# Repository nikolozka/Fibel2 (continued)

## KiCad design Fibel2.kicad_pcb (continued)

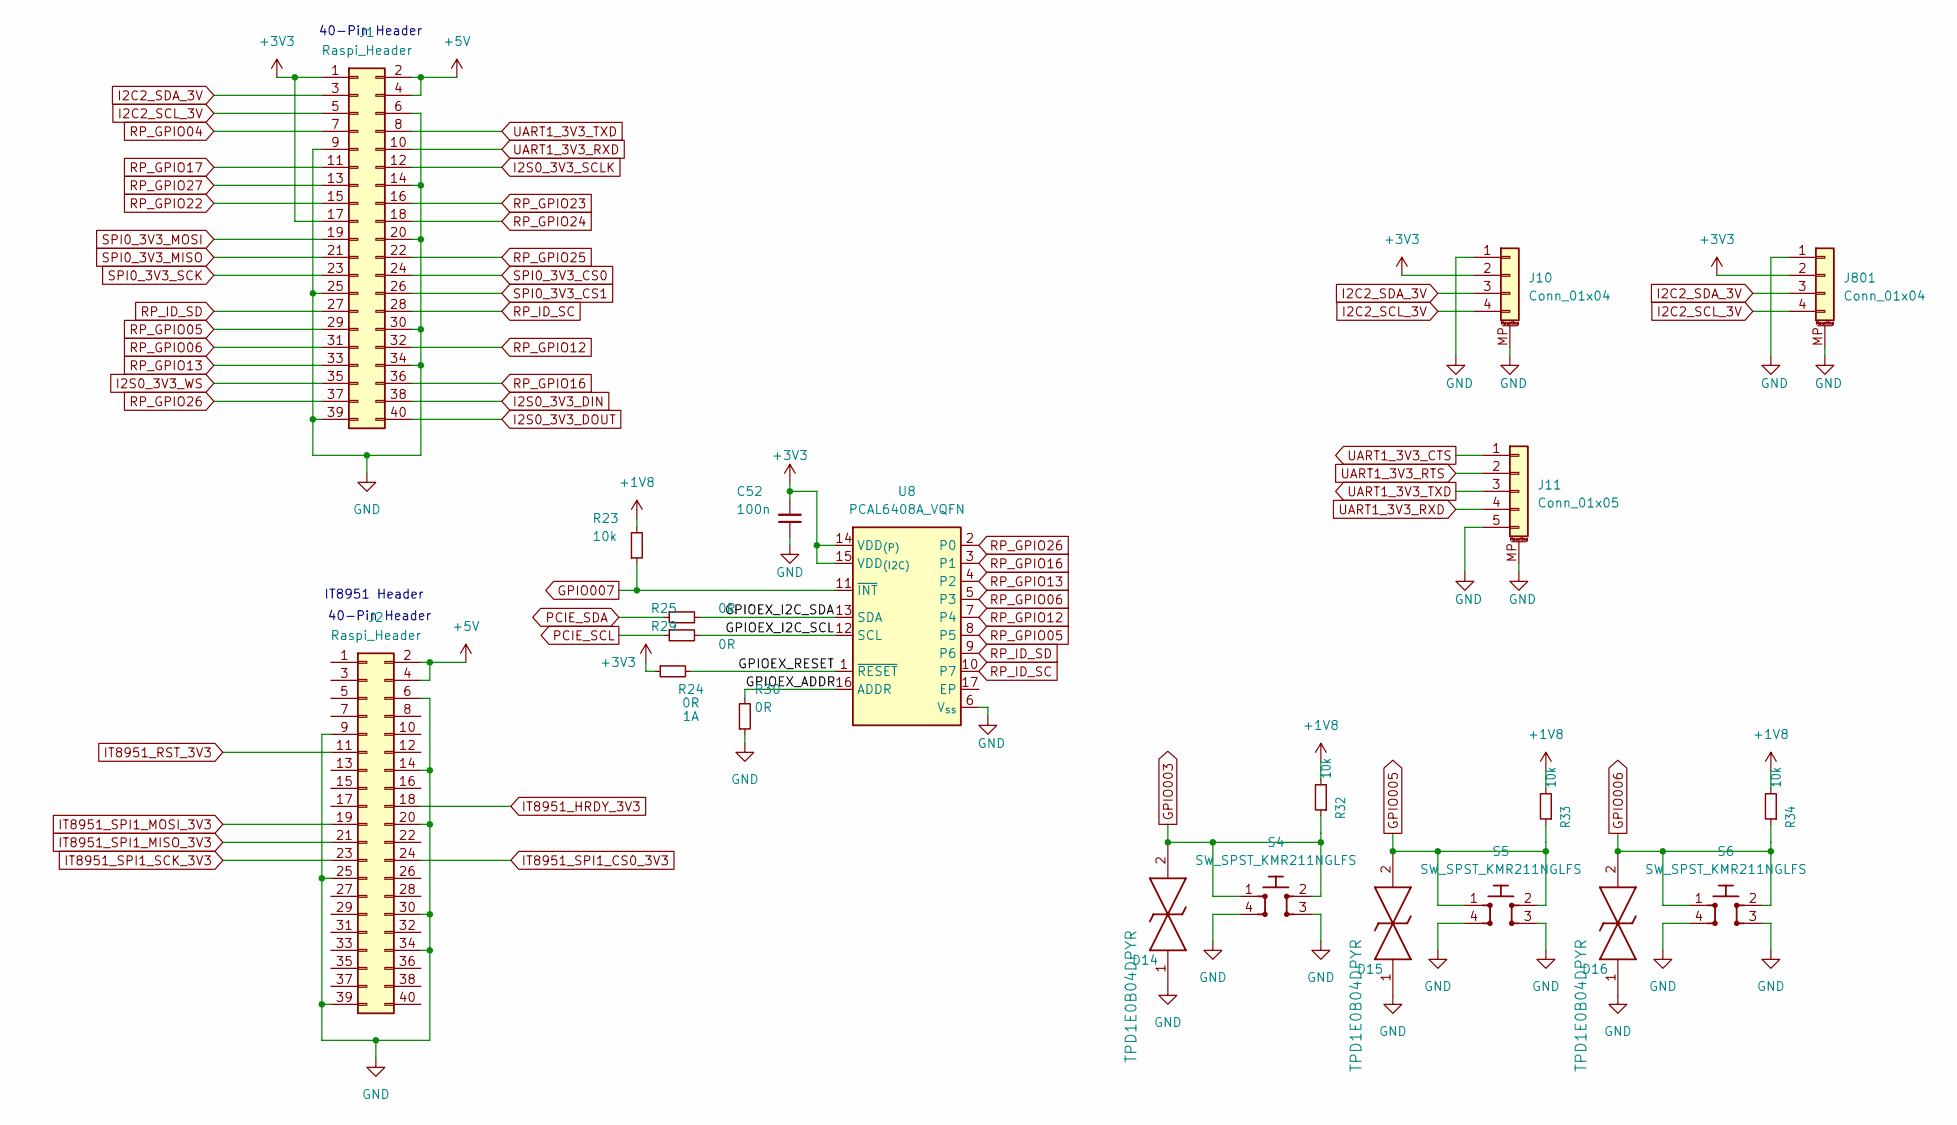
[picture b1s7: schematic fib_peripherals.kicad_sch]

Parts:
C52: C_Small_Rota; C_0402_1005Metric; Voltage 50V; MPN GRM155R61H104KE14D
D14, D15, D16: TPD1E0B04_XDFN-2; TPD1E0B04DPYT; MPN TPD1E0B04DPYR; Mouser Part Number 595-TPD1E0B04DPYT
J1, J2: Raspi_Header; Raspberry_Bottom_Entry
J10, J801: Conn_01x04; JST_PH_S4B-PH-SM4-TB_1x04-1MP_P2.00mm_Horizontal
J11: Conn_01x05; JST_PH_S5B-PH-SM4-TB_1x05-1MP_P2.00mm_Horizontal
R23: R_Small_Rota; R_0402_1005Metric; Tolerance 1%; MPN CR0402-FX-1002GLF
R24, R25, R29, R30: R_Small_Rota; R_0402_1005Metric; MPN ERJ2GE0R00X
R32, R33, R34: 10k; R_0402_1005Metric
S4, S5, S6: SW_SPST_KMR211NGLFS; KMR211NGLFS; MPN KMR211NGLFS
U8: PCAL6408A_VQFN; QFN50P300X300X100-17N; MPN PCAL6408ABSHP

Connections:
+1V8: R23.2, R32.2, R33.2, R34.2; also elsewhere on the board
+3V3: C52.2, J1.1, J1.17, J10.2, J801.2, R24.1, U8.14 (VDD_{(P)}), U8.15 (VDD_{(I2C)}); also elsewhere on the board
+5V: J1.2, J1.4, J2.2, J2.4; also elsewhere on the board
/Peripherals/GPIOEX_ADDR: R30.2, U8.16 (ADDR)
/Peripherals/GPIOEX_I2C_SCL: R29.2, U8.12 (SCL)
/Peripherals/GPIOEX_I2C_SDA: R25.2, U8.13 (SDA)
/Peripherals/GPIOEX_RESET: R24.2, U8.1 (~RESET)
GND: C52.1, D14.1, D15.1, D16.1, J1.6, J1.9, J1.14, J1.20, J1.25, J1.30, J1.34, J1.39, J2.6, J2.9, J2.14, J2.20, J2.25, J2.30, J2.34, J2.39, J10.1, J10.MP (MountPin), J11.5, J11.MP (MountPin), J801.1, J801.MP (MountPin), R30.1, S4.3, S4.4, S5.3, S5.4, S6.3, S6.4, U8.6 (V_{ss}); also elsewhere on the board
GPIO003: D14.2, R32.1, S4.1, S4.2; also elsewhere on the board
GPIO005: D15.2, R33.1, S5.1, S5.2; also elsewhere on the board
GPIO006: D16.2, R34.1, S6.1, S6.2; also elsewhere on the board
GPIO007: R23.1, U8.11 (~INT); also elsewhere on the board
I2C2_SCL_3V: J1.5, J10.4, J801.4; also elsewhere on the board
I2C2_SDA_3V: J1.3, J10.3, J801.3; also elsewhere on the board
I2S0_3V3_DIN: J1.38; also elsewhere on the board
I2S0_3V3_DOUT: J1.40; also elsewhere on the board
I2S0_3V3_SCLK: J1.12; also elsewhere on the board
I2S0_3V3_WS: J1.35; also elsewhere on the board
IT8951_HRDY_3V3: J2.18; also elsewhere on the board
IT8951_RST_3V3: J2.11; also elsewhere on the board
IT8951_SPI1_CS0_3V3: J2.24; also elsewhere on the board
IT8951_SPI1_MISO_3V3: J2.21; also elsewhere on the board
IT8951_SPI1_MOSI_3V3: J2.19; also elsewhere on the board
IT8951_SPI1_SCK_3V3: J2.23; also elsewhere on the board
PCIE_SCL: R29.1; also elsewhere on the board
PCIE_SDA: R25.1; also elsewhere on the board
RP_GPIO04: J1.7; also elsewhere on the board
RP_GPIO05: J1.29, U8.8 (P5)
RP_GPIO06: J1.31, U8.5 (P3)
RP_GPIO12: J1.32, U8.7 (P4)
RP_GPIO13: J1.33, U8.4 (P2)
RP_GPIO16: J1.36, U8.3 (P1)
RP_GPIO17: J1.11; also elsewhere on the board
RP_GPIO22: J1.15; also elsewhere on the board
RP_GPIO23: J1.16; also elsewhere on the board
RP_GPIO24: J1.18; also elsewhere on the board
RP_GPIO25: J1.22; also elsewhere on the board
RP_GPIO26: J1.37, U8.2 (P0)
RP_GPIO27: J1.13; also elsewhere on the board
RP_ID_SC: J1.28, U8.10 (P7)
RP_ID_SD: J1.27, U8.9 (P6)
SPI0_3V3_CS0: J1.24; also elsewhere on the board
SPI0_3V3_CS1: J1.26; also elsewhere on the board
SPI0_3V3_MISO: J1.21; also elsewhere on the board
SPI0_3V3_MOSI: J1.19; also elsewhere on the board
SPI0_3V3_SCK: J1.23; also elsewhere on the board
UART1_3V3_CTS: J11.1; also elsewhere on the board
UART1_3V3_RTS: J11.2; also elsewhere on the board
UART1_3V3_RXD: J1.10, J11.4; also elsewhere on the board
UART1_3V3_TXD: J1.8, J11.3; also elsewhere on the board

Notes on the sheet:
40-Pin Header
IT8951 Header

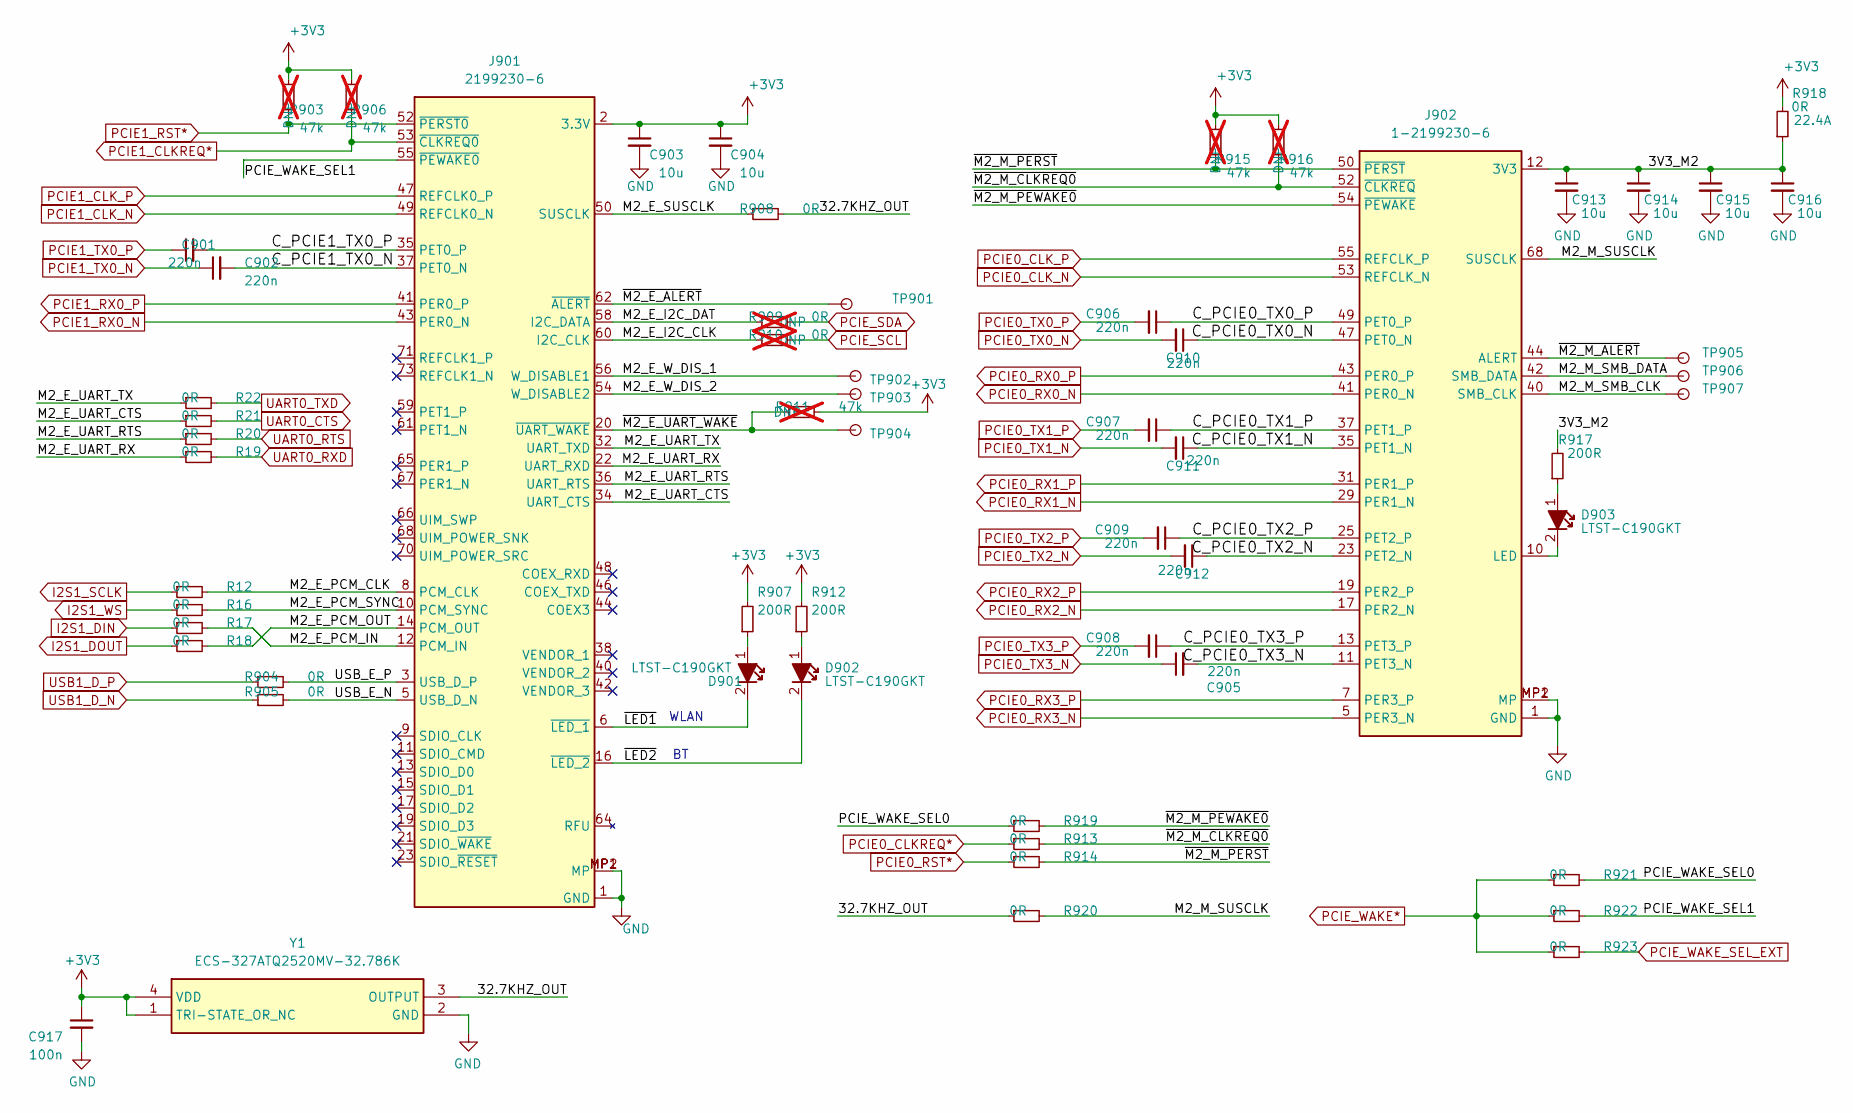
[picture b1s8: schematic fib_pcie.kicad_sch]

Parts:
C901, C902, C905, C906, C907, C908, C909, C910, C911, C912: 220nF; C_0402_1005Metric; MPN CC0402KRX5R6BB224
C903, C904, C913, C914, C915, C916: 20uF; C_0603_1608Metric; MPN GRM188R61A106KE69D
C917: 100nF; C_0402_1005Metric; Voltage 50V; MPN GRM155R61H104KE14D
D901, D902, D903: LED_G_0603_LTST-C190GKT; LED_0603_1608Metric; MPN LTST-C190GKT
J901: Bus_M.2_2199230-6; 21992306; MPN 2199230-6
J902: Bus_M.2_1-2199230-6; 121992306; MPN 1-2199230-6
R12, R16, R17, R18, R19, R20, R21, R22, R913, R914, R919, R920, R921, R922, R923: R_Small_Rota; R_0402_1005Metric; MPN ERJ2GE0R00X
R903, R906, R911, R915, R916: 47K; R_0402_1005Metric; Tolerance 1%; MPN CR0402-FX-4702GLF; not fitted
R904, R905, R908: 0R; R_0402_1005Metric; MPN ERJ2GE0R00X
R907, R912, R917: 200R; R_0402_1005Metric; Tolerance 1%; MPN CR0402-FX-2000GLF
R909, R910: 0R; R_0402_1005Metric; MPN ERJ2GE0R00X; not fitted
R918: 0R 22A; R_0402_1005Metric; MPN PMR03EZPJ000
TP901, TP902, TP903, TP904, TP905, TP906, TP907: TestPoint; TestPoint_Pad_D1.0mm
Y1: ECS-327ATQ2520MV-32.786K; ECS2520MV; Mouser Part Number 520-327ATQ2520MVBSTR

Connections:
+3V3: C903.1, C904.1, C917.1, J901.2 (3.3V), J901.4 (3.3V), J901.72 (3.3V), J901.74 (3.3V), R903.1, R906.1, R907.2, R911.2, R912.2, R915.1, R916.1, R918.2, Y1.1 (TRI-STATE_OR_NC), Y1.4 (VDD); also elsewhere on the board
/PCIe/3V3_M2: C913.1, C914.1, C915.1, C916.1, J902.2 (3V3), J902.4 (3V3), J902.12 (3V3), J902.14 (3V3), J902.16 (3V3), J902.18 (3V3), J902.70 (3V3), J902.72 (3V3), J902.74 (3V3), R917.2, R918.1
/PCIe/32.7KHZ_OUT: R908.2, R920.1, Y1.3 (OUTPUT)
/PCIe/C_PCIE0_TX0_N: C910.1, J902.47 (PET0_N)
/PCIe/C_PCIE0_TX0_P: C906.1, J902.49 (PET0_P)
/PCIe/C_PCIE0_TX1_N: C911.1, J902.35 (PET1_N)
/PCIe/C_PCIE0_TX1_P: C907.1, J902.37 (PET1_P)
/PCIe/C_PCIE0_TX2_N: C912.1, J902.23 (PET2_N)
/PCIe/C_PCIE0_TX2_P: C909.1, J902.25 (PET2_P)
/PCIe/C_PCIE0_TX3_N: C905.2, J902.11 (PET3_N)
/PCIe/C_PCIE0_TX3_P: C908.1, J902.13 (PET3_P)
/PCIe/C_PCIE1_TX0_N: C902.2, J901.37 (PET0_N)
/PCIe/C_PCIE1_TX0_P: C901.2, J901.35 (PET0_P)
/PCIe/M2_E_I2C_CLK: J901.60 (I2C_CLK), R910.1
/PCIe/M2_E_I2C_DAT: J901.58 (I2C_DATA), R909.1
/PCIe/M2_E_PCM_CLK: J901.8 (PCM_CLK), R12.2
/PCIe/M2_E_PCM_IN: J901.12 (PCM_IN), R17.2
/PCIe/M2_E_PCM_OUT: J901.14 (PCM_OUT), R18.2
/PCIe/M2_E_PCM_SYNC: J901.10 (PCM_SYNC), R16.2
/PCIe/M2_E_SUSCLK: J901.50 (SUSCLK), R908.1
/PCIe/M2_E_UART_CTS: J901.34 (UART_CTS), R21.1
/PCIe/M2_E_UART_RTS: J901.36 (UART_RTS), R20.1
/PCIe/M2_E_UART_RX: J901.22 (UART_RXD), R19.1
/PCIe/M2_E_UART_TX: J901.32 (UART_TXD), R22.1
/PCIe/M2_E_W_DIS_1: J901.56 (W_DISABLE1), TP902.1
/PCIe/M2_E_W_DIS_2: J901.54 (W_DISABLE2), TP903.1
/PCIe/M2_M_SMB_CLK: J902.40 (SMB_CLK), TP907.1
/PCIe/M2_M_SMB_DATA: J902.42 (SMB_DATA), TP906.1
/PCIe/M2_M_SUSCLK: J902.68 (SUSCLK), R920.2
/PCIe/PCIE_WAKE_SEL0: R919.1, R921.2
/PCIe/PCIE_WAKE_SEL1: J901.55 (~PEWAKE0), R922.2
/PCIe/USB_E_N: J901.5 (USB_D_N), R905.2
/PCIe/USB_E_P: J901.3 (USB_D_P), R904.2
/PCIe/~LED1: D901.2, J901.6 (~LED_1)
/PCIe/~LED2: D902.2, J901.16 (~LED_2)
/PCIe/~M2_E_ALERT: J901.62 (~ALERT), TP901.1
/PCIe/~M2_E_UART_WAKE: J901.20 (~UART_WAKE), R911.1, TP904.1
/PCIe/~M2_M_ALERT: J902.44 (ALERT), TP905.1
/PCIe/~M2_M_CLKREQ0: J902.52 (~CLKREQ), R913.2, R916.2
/PCIe/~M2_M_PERST: J902.50 (~PERST), R914.2, R915.2
/PCIe/~M2_M_PEWAKE0: J902.54 (~PEWAKE), R919.2
GND: C903.2, C904.2, C913.2, C914.2, C915.2, C916.2, C917.2, J901.1 (GND), J901.7 (GND), J901.18 (GND), J901.33 (GND), J901.39 (GND), J901.45 (GND), J901.51 (GND), J901.57 (GND), J901.63 (GND), J901.69 (GND), J901.75 (GND), J901.MP1 (MP), J901.MP2 (MP), J902.1 (GND), J902.3 (GND), J902.9 (GND), J902.15 (GND), J902.21 (GND), J902.27 (GND), J902.33 (GND), J902.39 (GND), J902.45 (GND), J902.51 (GND), J902.57 (GND), J902.71 (GND), J902.73 (GND), J902.75 (GND), J902.MP1 (MP), J902.MP2 (MP), Y1.2 (GND); also elsewhere on the board
I2S1_DIN: R17.1; also elsewhere on the board
I2S1_DOUT: R18.1; also elsewhere on the board
I2S1_SCLK: R12.1; also elsewhere on the board
I2S1_WS: R16.1; also elsewhere on the board
unnamed: D901.1, R907.1
unnamed: D902.1, R912.1
unnamed: D903.1, R917.1
unnamed: D903.2, J902.10 (LED)
PCIE0_CLKREQ*: R913.1; also elsewhere on the board
PCIE0_CLK_N: J902.53 (REFCLK_N); also elsewhere on the board
PCIE0_CLK_P: J902.55 (REFCLK_P); also elsewhere on the board
PCIE0_RST*: R914.1; also elsewhere on the board
PCIE0_RX0_N: J902.41 (PER0_N); also elsewhere on the board
PCIE0_RX0_P: J902.43 (PER0_P); also elsewhere on the board
PCIE0_RX1_N: J902.29 (PER1_N); also elsewhere on the board
PCIE0_RX1_P: J902.31 (PER1_P); also elsewhere on the board
PCIE0_RX2_N: J902.17 (PER2_N); also elsewhere on the board
PCIE0_RX2_P: J902.19 (PER2_P); also elsewhere on the board
PCIE0_RX3_N: J902.5 (PER3_N); also elsewhere on the board
PCIE0_RX3_P: J902.7 (PER3_P); also elsewhere on the board
PCIE0_TX0_N: C910.2; also elsewhere on the board
PCIE0_TX0_P: C906.2; also elsewhere on the board
PCIE0_TX1_N: C911.2; also elsewhere on the board
PCIE0_TX1_P: C907.2; also elsewhere on the board
PCIE0_TX2_N: C912.2; also elsewhere on the board
PCIE0_TX2_P: C909.2; also elsewhere on the board
PCIE0_TX3_N: C905.1; also elsewhere on the board
PCIE0_TX3_P: C908.2; also elsewhere on the board
PCIE1_CLKREQ*: J901.53 (~CLKREQ0), R906.2; also elsewhere on the board
PCIE1_CLK_N: J901.49 (REFCLK0_N); also elsewhere on the board
PCIE1_CLK_P: J901.47 (REFCLK0_P); also elsewhere on the board
PCIE1_RST*: J901.52 (~PERST0), R903.2; also elsewhere on the board
PCIE1_RX0_N: J901.43 (PER0_N); also elsewhere on the board
PCIE1_RX0_P: J901.41 (PER0_P); also elsewhere on the board
PCIE1_TX0_N: C902.1; also elsewhere on the board
PCIE1_TX0_P: C901.1; also elsewhere on the board
PCIE_SCL: R910.2; also elsewhere on the board
PCIE_SDA: R909.2; also elsewhere on the board
PCIE_WAKE*: R921.1, R922.1, R923.1; also elsewhere on the board
PCIE_WAKE_SEL_EXT: R923.2
UART0_CTS: R21.2; also elsewhere on the board
UART0_RTS: R20.2; also elsewhere on the board
UART0_RXD: R19.2; also elsewhere on the board
UART0_TXD: R22.2; also elsewhere on the board
USB1_D_N: R905.1; also elsewhere on the board
USB1_D_P: R904.1; also elsewhere on the board

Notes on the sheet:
WLAN

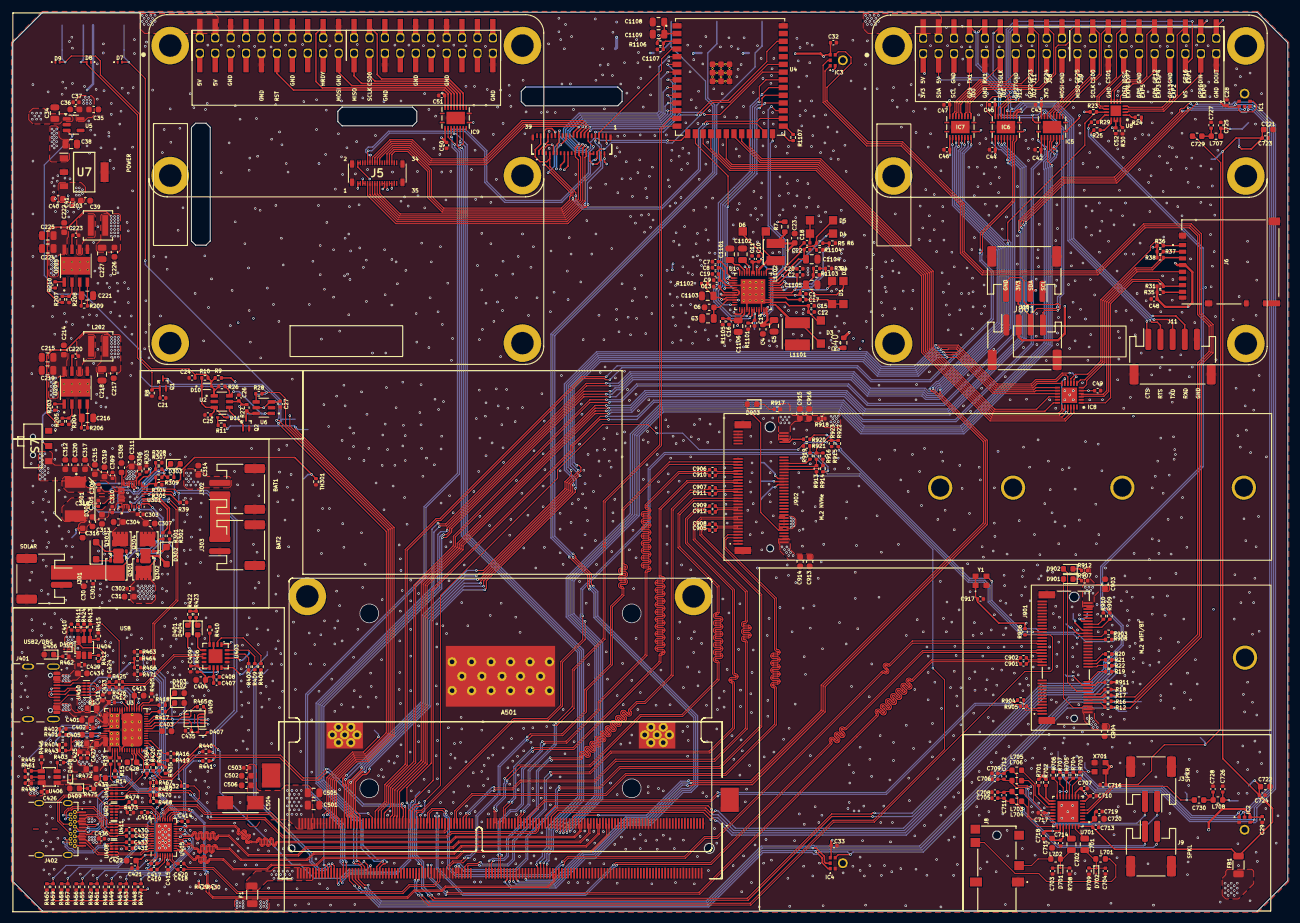
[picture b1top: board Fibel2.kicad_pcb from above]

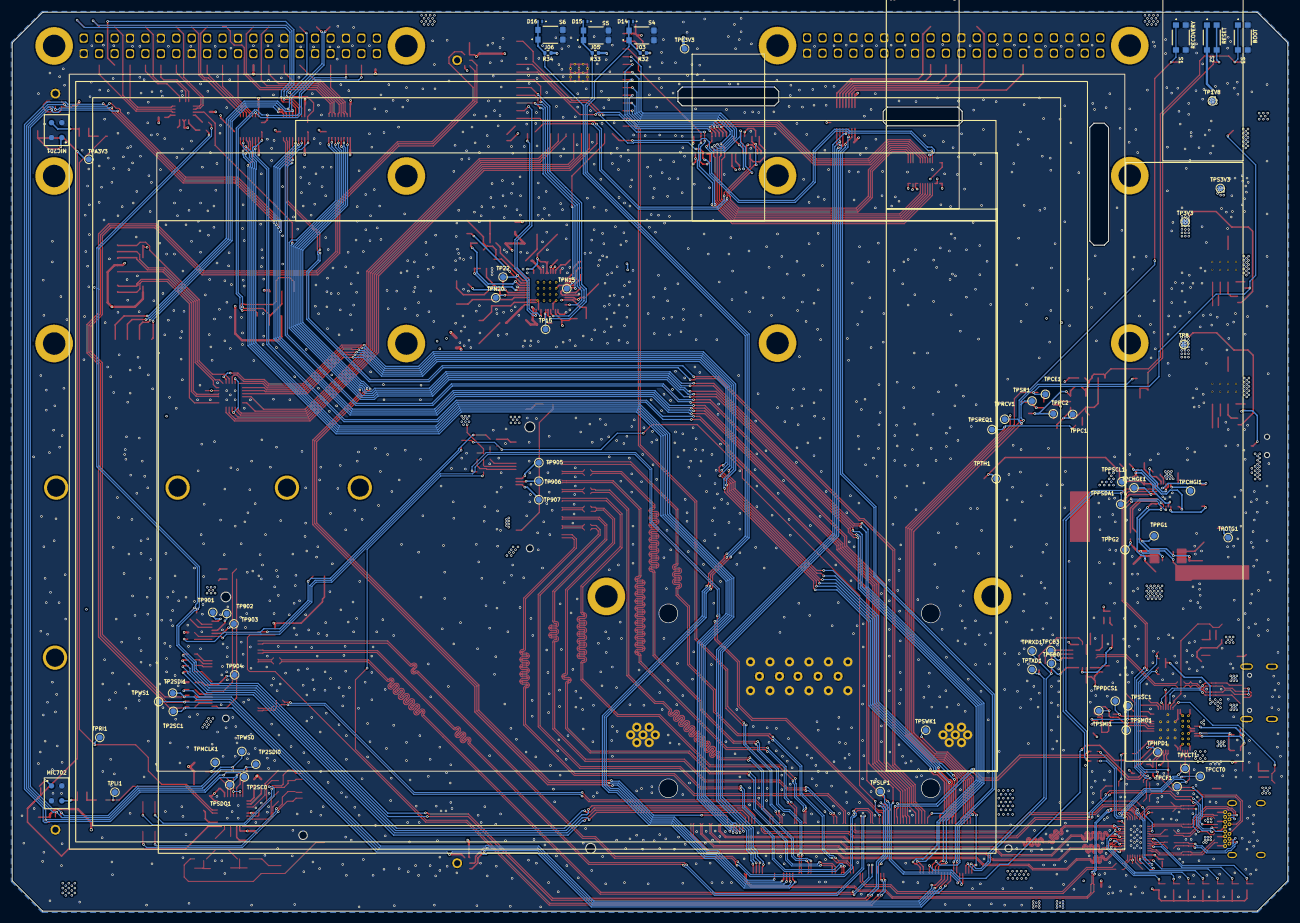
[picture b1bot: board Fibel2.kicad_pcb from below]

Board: 4 copper layers, 210.0 x 148.0 mm, 514 parts (70 on the bottom side), 427 nets.

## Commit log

2024-04-29 added documentation for Orin and other ics i'm planning to use, created hierarchy for schematics
2024-05-04 added several ICs, implementted schematics for charger, boost converter and LDOs
2024-05-04 added symbol&footprint for orin/sodimm, added a bunch of specs and docs, partially implemented audio, full steam ahead
2024-05-20 added usb+PD+DP & pcie implementations from antmicro design, added specs for USB components, rethought power+usb arch
2024-05-20 added footprint, symbol and model for TPS65987
2024-05-29 added nets for 40 pin headers (epd & rpi header) connected some of the nets i'm reeusing
2024-05-29 added net labels for pcie (m&e key), reusing a lot of blocks from antmicro
2024-06-05 continuing schematic work for pcie and other high speed interfaces
2024-06-05 renamed /Fib2_Docs/AUX to Others because windows is being a lil bitch
2024-06-17 restructured EPD side of things, replaced rp2040 with esp32 s3 because of it's LCD controller, USB, LP WIFI_BT & EPDiy compat, repurposed USB0 for ESP interfacing, added e-ink pmic
2024-06-19 added notest regarding the audio codec
2024-06-19 added buck converter, refactoored peripherals and updated gpio/SPI/i2c mapping
2024-06-21 partially implemented E-INK PMIC
2024-06-21 added decoupling and inductors for EPD PMIC
2024-06-22 added connections to ESP32 S3, most oof EPD stuff that we're gooing to use is included
2024-06-23 refactored PCIe pages
2024-06-25 added some missing footprints, stared working ono power-on and sequencing
2024-06-29 started arranging the components on the board, added some more missing footprints. starting to think about the overall distribution of parts
2024-06-30 started routing the SODIMM, updated connector footprint, started arranging component into sub-areas
2024-06-30 did a ton of routing and modeling for SOM, USB, DP & Charging/Power, things starting to take shape
2024-07-02 did some work on the ports and layout
2024-07-05 implemented most of USB and Power Supplies
2024-07-07 did a big portion of pcie, optimized placement of components and subsections. power, usb and charging is largely done. still need to do length matching though. will need to take a second look at sche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
2024-07-07 further optimized placement, finished most of buck array, expanded pcie, added tons of missing footprints, diff pair spacing optimization
2024-07-08 90 percent done with routing. need to go over all schematic pages, double check everything thoroughly, do lengthmatching add any missing footprints, take care of startup, ferrites, audio, eink connec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
2024-07-11 replaced 1v8 buck with ldo, added startup circuit, added footprints for eink connectors
2024-07-12 added all missing footprints, fixed library & footprint links, did layout out 99% of components, all that's left is rtc(?), peripherals, routing & lengthmatching and final sanity checks
2024-07-12 removed redundant schematic files
2024-07-12 added gitignore
2024-07-12 added lck file to gitignore
2024-07-14 did length tuning, routing of final submodules and most of power routing
2024-07-14 added port expander and level shifters, routed peripherals fixed most drc errors, assigned gpios etc.
2024-07-16 routed epd displays, added testpoints and all the little checks and fixe, (regrettably) removed the i80 connector, 99% there, need to double check some things add peripheral connectors, shared-ish st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
2024-07-16 finished routing, sanity check and prep fabrication files next
2024-07-18 added second i2c, modified 40 pin headers
2024-07-19 adde testpoints, fixed power supplies, ready to order
2024-07-19 added gerbers
